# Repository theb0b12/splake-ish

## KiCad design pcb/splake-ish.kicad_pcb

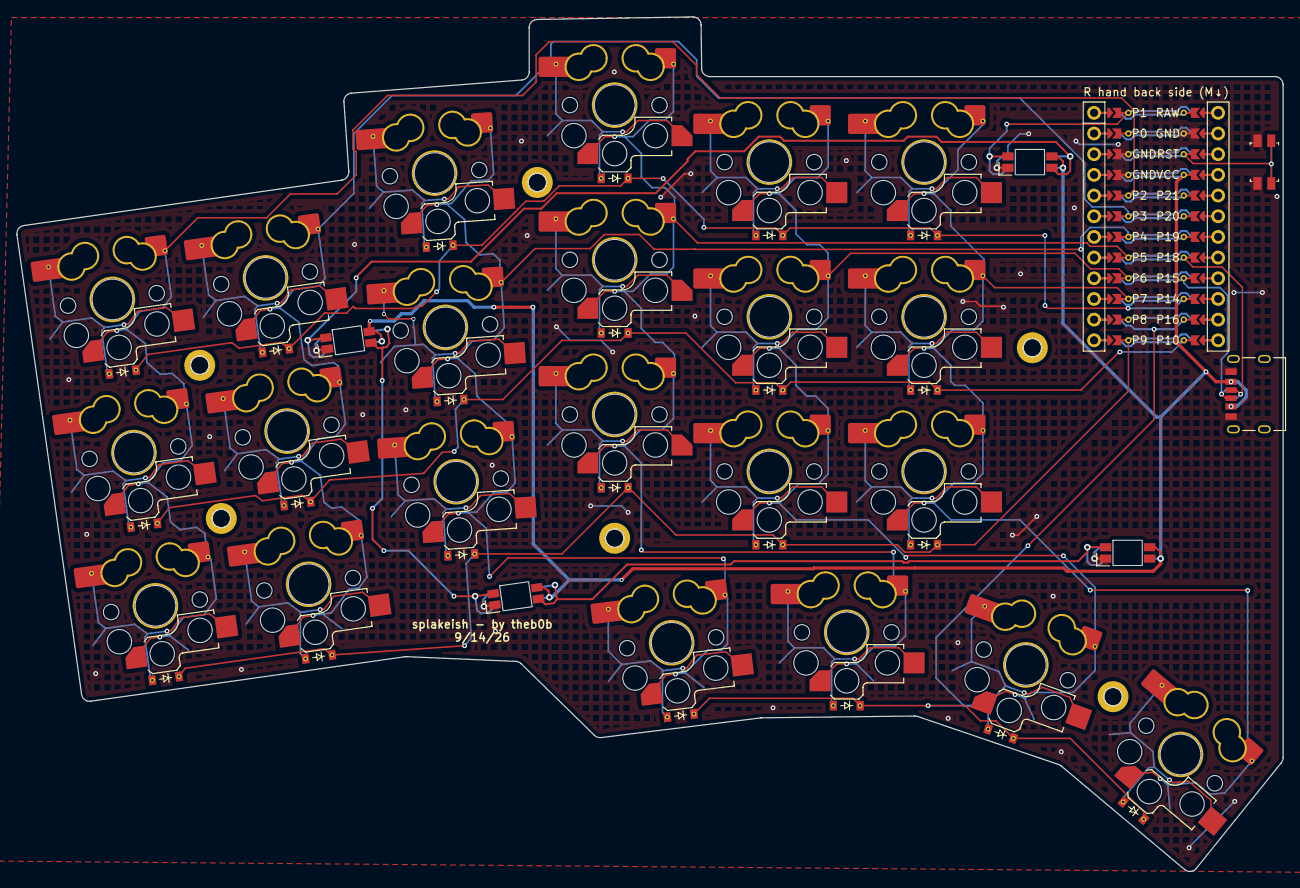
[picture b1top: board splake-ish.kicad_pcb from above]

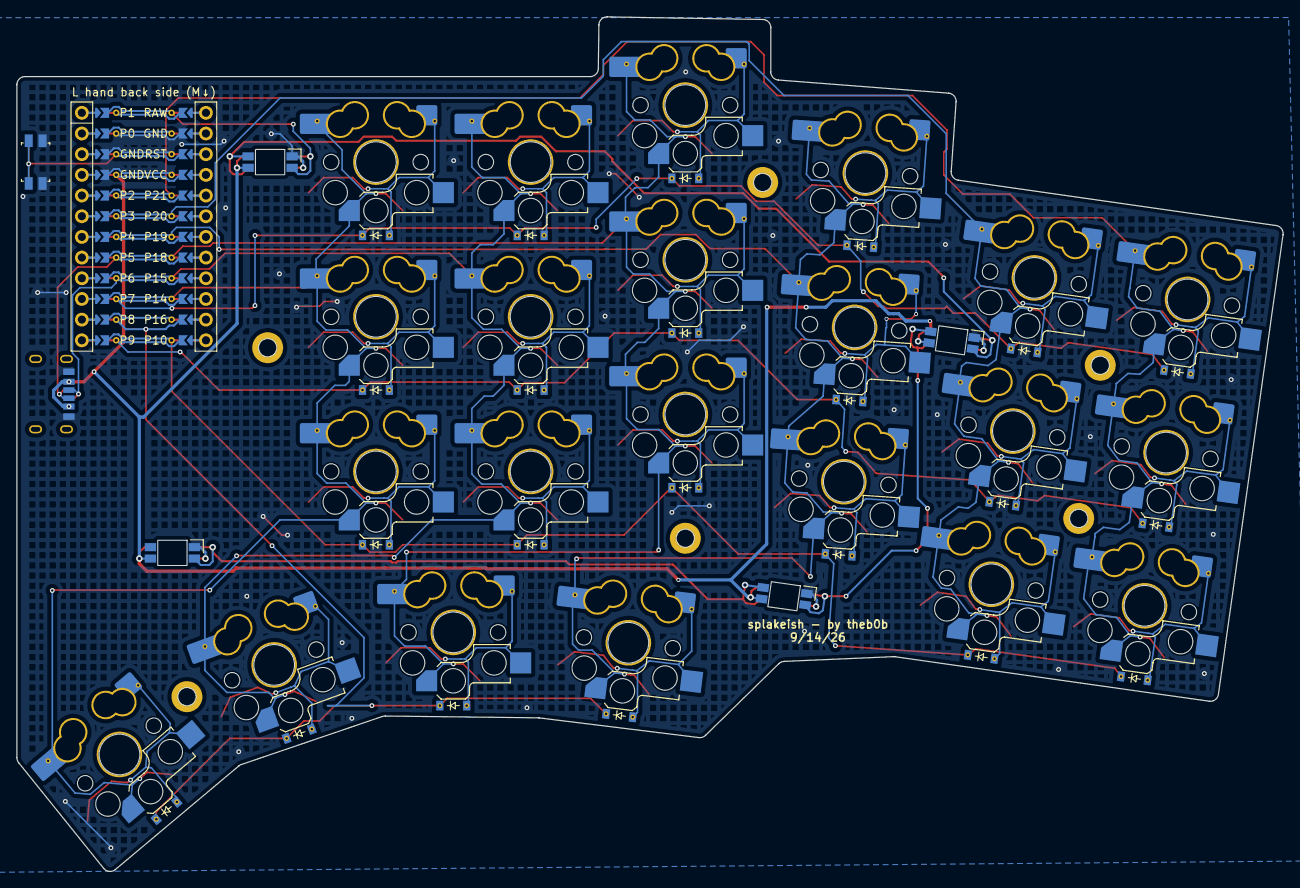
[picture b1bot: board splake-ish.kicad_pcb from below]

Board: 2 copper layers, 155.5 x 105.0 mm, 79 parts (48 on the bottom side), 41 nets.

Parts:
D1, D2, D3, D4, D5, D6, D7, D8, D9, D10, D11, D12, D13, D14, D15, D16, D17, D18, D19, D20, D21, D22: ComboDiode
H1, H2, H3, H4, H5, H6: mounting_hole_plated_withedgecut
LED1, LED2, LED3, LED4: led_SK6812mini-e (per-key, reversible)
MCU1: mcu_nice_nano
RST1: reset_switch_smd_side
S1, S2, S3, S4, S5, S6, S7, S8, S9, S10, S11, S12, S13, S14, S15, S16, S17, S18, S19, S20, S21, S22: switch_choc_v1_v2
S23, S24, S25, S26, S27, S28, S29, S30, S31, S32, S33, S34, S35, S36, S37, S38, S39, S40, S41, S42, S43, S44: switch_gateron_ks27_ks33
XX1: CUI_UJC-HP2-3-SMT-TR

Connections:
1_r1: D19.1, D19.2, S19.2, S41.2
1_r1_thumb2: D22.1, D22.2, S22.2, S44.2
2_r1: D20.1, D20.2, S20.2, S42.2
3_r1: D21.1, D21.2, S21.2, S43.2
CC1: MCU1.109, XX1.A5, XX1.B5
CC2: MCU1.108, XX1.A5, XX1.B5
GND: LED1.3, LED2.3, LED3.3, LED4.3, MCU1.102, MCU1.121, MCU1.122, RST1.2, RST1.4, XX1.A12, XX1.B12
P1: LED3.4, MCU1.124
P2: MCU1.120, S1.1, S2.1, S3.1, S23.1, S24.1, S25.1
P3: MCU1.119, S4.1, S5.1, S6.1, S26.1, S27.1, S28.1
P4: MCU1.118, S7.1, S8.1, S9.1, S22.1, S29.1, S30.1, S31.1, S44.1
P5: MCU1.117, S10.1, S11.1, S12.1, S19.1, S32.1, S33.1, S34.1, S41.1
P6: MCU1.116, S13.1, S14.1, S15.1, S20.1, S35.1, S36.1, S37.1, S42.1
P7: MCU1.115, S16.1, S17.1, S18.1, S21.1, S38.1, S39.1, S40.1, S43.1
P9: D1.1, D4.1, D7.1, D10.1, D13.1, D16.1, MCU1.113
P10: D2.1, D5.1, D8.1, D11.1, D14.1, D17.1, MCU1.112
P14: D3.1, D6.1, D9.1, D12.1, D15.1, D18.1, MCU1.110
P16: D19.1, D20.1, D21.1, D22.1, MCU1.111
RST: MCU1.103, RST1.1, RST1.3
VCC: LED1.1, LED2.1, LED3.1, LED4.1, MCU1.104, XX1.A9, XX1.B9
index_r1: D13.1, D13.2, S13.2, S35.2
index_r2: D14.1, D14.2, S14.2, S36.2
index_r3: D15.1, D15.2, S15.2, S37.2
inner_r1: D16.1, D16.2, S16.2, S38.2
inner_r2: D17.1, D17.2, S17.2, S39.2
inner_r3: D18.1, D18.2, S18.2, S40.2
led1: LED1.4, LED3.2
led2: LED1.2, LED2.4
led3: LED2.2, LED4.4
middle_r1: D10.1, D10.2, S10.2, S32.2
middle_r2: D11.1, D11.2, S11.2, S33.2
middle_r3: D12.1, D12.2, S12.2, S34.2
outer-pinky_r1: D1.1, D1.2, S1.2, S23.2
outer-pinky_r2: D2.1, D2.2, S2.2, S24.2
outer-pinky_r3: D3.1, D3.2, S3.2, S25.2
pinky_r1: D4.1, D4.2, S4.2, S26.2
pinky_r2: D5.1, D5.2, S5.2, S27.2
pinky_r3: D6.1, D6.2, S6.2, S28.2
ring_r1: D7.1, D7.2, S7.2, S29.2
ring_r2: D8.1, D8.2, S8.2, S30.2
ring_r3: D9.1, D9.2, S9.2, S31.2
